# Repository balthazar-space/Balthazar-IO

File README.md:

# Balthazar

Open-hardware laptop computer modules description and concept.

These are electronic schematic modules as presented at https://balthazar.space/wiki/Balthazar with the main aim for team access. See the [main repository](https://github.com/balthazar-space/balthazar) for other designs.

# Balthazar IO

BalthazarIO module is a simple USB2.0 four-port hub for the internal devices: keyboard and touchpad, webcam and optional audiocard. Additional simplification and pcb size reduction was done recently.

IO-board (here) means connectivity with peripheral devices. These can be seen as on-board and out-board. On-board Balthazar devices include: combined usb1.1 keyboard + trackpad, usb2.0 webcam and optional audio-card. 

Since we are targeting the mini-computer family of systems (Raspberry PI. Banana PI, Orange PI, ...) - USB is the usual solution for this. 

A simple usb 2.0 hub is enough, so a very ubiquitous usb hub chip was chosen. Main mini-computer board usually provides a much better hub for 4 downstream usb devices. At this point this is still mainly USB 2.x - slowly moving to usb3.x.

Mass storage / system disk - microSD – and especially versions of SSD (sata or pcie) – should be plugged to usb3.x directly (via usb adapter).

KiCad 5.1.5 files are uploaded here as well as the drawings and pictures.

## License

All resources licensed under the CERN Open Hardware Licence CERN-OHL W V.2.0

Version 2.0 of the CERN-OHL introduces three variants of the licence – strongly (S) reciprocal, weakly (W) reciprocal and permissive (P) – which aim to address specific constraints caused by different collaboration models currently used in open-hardware projects. 

The first two variants mean that if any product is made using an open hardware design, the design of that product, including any improvements or modifications, should be made available under the same licence as that of the original product. Permissive licences do not impose this condition.

See the [LICENSE.md](./LICENSE.md) file for more information.

## Funding

This project is funded through the [NGI Zero Entrust Fund](https://nlnet.nl/entrust), a fund
established by [NLnet](https://nlnet.nl) with financial support from the European Commission's
[Next Generation Internet](https://ngi.eu) program. Learn more on the [NLnet project page](https://nlnet.nl/project/Balthazar-Casing/).

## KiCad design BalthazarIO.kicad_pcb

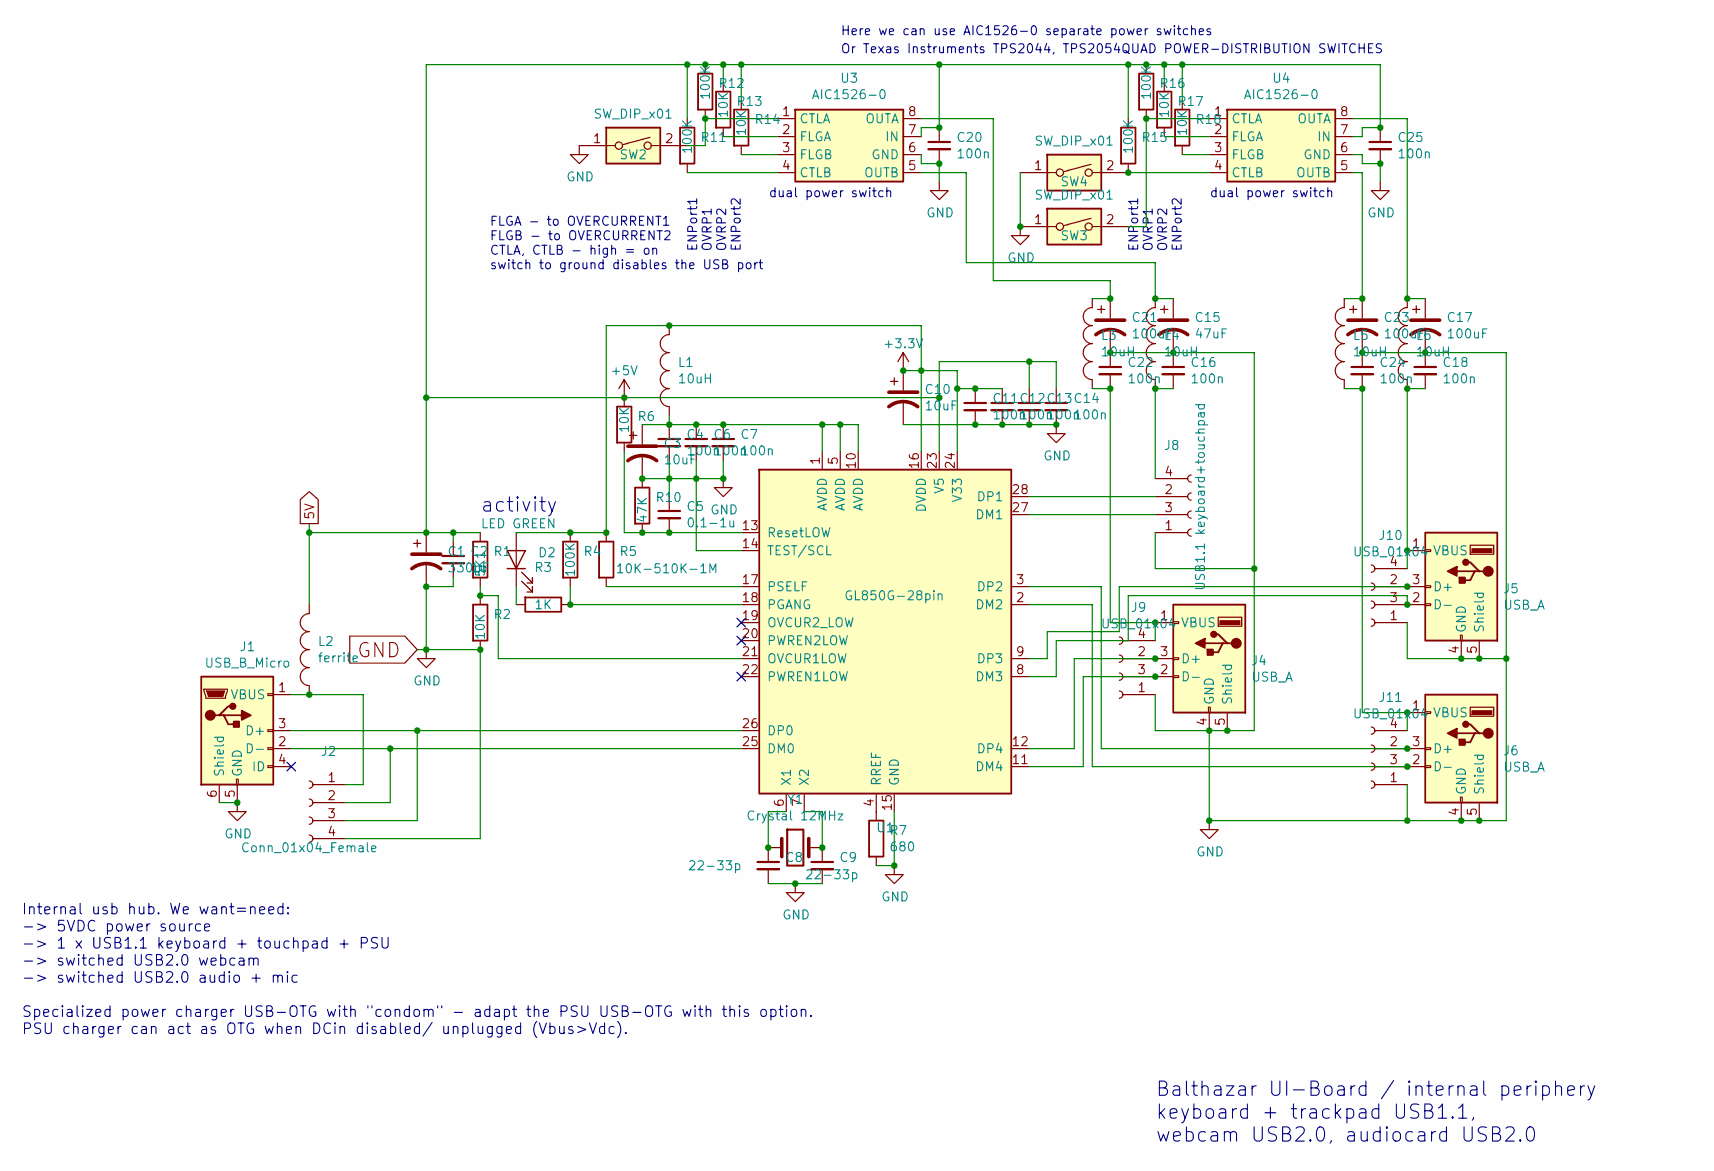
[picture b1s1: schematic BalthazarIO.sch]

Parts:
C1: 330uF; CP_Radial_D6.3mm_P2.50mm
C2: 1u; C_1206_3216Metric
C3, C10: 10uF; C_1206_3216Metric
C4, C6, C7, C11, C12, C13, C14, C16, C18, C20, C22, C24, C25: 100n; C_1206_3216Metric
C5: 0.1-1u; C_1206_3216Metric
C8, C9: 22-33p; C_1206_3216Metric
C15: 47uF; CP_Radial_D5.0mm_P2.50mm
C17, C21, C23: 100uF; CP_Radial_D5.0mm_P2.50mm
D2: LED GREEN; LED_1206_3216Metric
J1: USB_B_Micro; USB_Micro-AB_Molex_47590-0001
J2: Conn_01x04_Female; PinSocket_1x04_P2.54mm_Horizontal
J4, J5, J6: USB_A; USB_A_CNCTech_1001-011-01101_Horizontal
J8: USB1.1 keyboard+touchpad; PinSocket_1x04_P2.54mm_Horizontal
J9, J10, J11: USB_01x04; PinSocket_1x04_P2.54mm_Horizontal
L1, L3, L4, L5, L6: 10uH; L_1206_3216Metric
L2: ferrite; L_1206_3216Metric
R1: 5K1; R_1206_3216Metric
R2, R6, R13, R14, R17, R18: 10K; R_1206_3216Metric
R3: 1K; R_1206_3216Metric
R4, R11, R12, R15, R16: 100K; R_1206_3216Metric
R5: 10K-510K-1M; R_1206_3216Metric
R7: 680; R_1206_3216Metric
R10: 47K; R_1206_3216Metric
SW2, SW3, SW4: SW_DIP_x01; SW_DIP_SPSTx01_Slide_9.78x4.72mm_W7.62mm_P2.54mm
U1: GL850G-28pin; SSOP-28_5.3x10.2mm_P0.65mm
U3, U4: AIC1526-0; SOP-8_3.9x4.9mm_P1.27mm
Y1: Crystal 12MHz; Crystal_HC50_Vertical

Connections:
5V: C1.1, C2.1, C13.1, C14.1, C20.1, C25.1, L2.2, R1.1, R6.1, R11.1, R12.1, R13.1, R14.1, R15.1, R16.1, R17.1, R18.1, U1.23 (V5), U3.7 (IN), U4.7 (IN)
+3V3: C10.1, C11.1, C12.1, D2.2 (A), L1.2, R4.1, R5.1, U1.16 (DVDD), U1.24 (V33)
GND: C1.2, C2.2, C3.2, C4.2, C5.1, C6.2, C7.2, C8.2, C9.2, C10.2, C11.2, C12.2, C13.2, C14.2, C15.2, C16.1, C17.2, C18.1, C20.2, C21.2, C22.1, C23.2, C24.1, C25.2, J1.5 (GND), J1.6 (Shield), J2.4, J4.4 (GND), J4.5 (Shield), J5.4 (GND), J5.5 (Shield), J6.4 (GND), J6.5 (Shield), J8.1 (Vbus), J9.1 (Vbus), J10.1 (Vbus), J11.1 (Vbus), R2.2, R7.2, R10.1, SW2.1, SW3.1, SW4.1, U1.14 (TEST/SCL), U1.15 (GND), U3.6 (GND), U4.6 (GND)
unnamed: C3.1, C4.1, C6.1, C7.1, L1.1, U1.1 (AVDD), U1.5 (AVDD), U1.10 (AVDD)
unnamed: C5.2, R6.2, R10.2, U1.13 (ResetLOW)
unnamed: C8.1, U1.6 (X1), Y1.1
unnamed: C9.1, U1.7 (X2), Y1.2
unnamed: C15.1, L4.2, U3.5 (OUTB)
unnamed: C16.2, J8.4 (gnd), L4.1
unnamed: C17.1, L6.2, U4.8 (OUTA)
unnamed: C18.2, J5.1 (VBUS), J10.4 (gnd), L6.1
unnamed: C21.1, L3.2, U3.8 (OUTA)
unnamed: C22.2, J4.1 (VBUS), J9.4 (gnd), L3.1
unnamed: C23.1, L5.2, U4.5 (OUTB)
unnamed: C24.2, J6.1 (VBUS), J11.4 (gnd), L5.1
unnamed: D2.1 (K), R3.2
unnamed: J1.1 (VBUS), J2.1, L2.1
unnamed: J1.2 (D-), J2.2, U1.25 (DM0)
unnamed: J1.3 (D+), J2.3, U1.26 (DP0)
unnamed: J4.2 (D-), J9.3, U1.11 (DM4)
unnamed: J4.3 (D+), J9.2, U1.12 (DP4)
unnamed: J8.2, U1.28 (DP1)
unnamed: J8.3, U1.27 (DM1)
unnamed: J5.3 (D+), J10.2, U1.9 (DP3)
unnamed: J5.2 (D-), J10.3, U1.8 (DM3)
unnamed: J6.3 (D+), J11.2, U1.3 (DP2)
unnamed: J6.2 (D-), J11.3, U1.2 (DM2)
unnamed: R1.2, R2.1, U1.21 (OVCUR1LOW)
unnamed: R3.1, R4.2, U1.18 (PGANG)
unnamed: R5.2, U1.17 (PSELF)
unnamed: R7.1, U1.4 (RREF)
unnamed: R11.2, U3.4 (CTLB)
unnamed: R12.2, SW2.2, U3.1 (CTLA)
unnamed: R13.2, U3.2 (FLGA)
unnamed: R14.2, U3.3 (FLGB)
unnamed: R15.2, SW4.2, U4.4 (CTLB)
unnamed: R16.2, SW3.2, U4.1 (CTLA)
unnamed: R17.2, U4.2 (FLGA)
unnamed: R18.2, U4.3 (FLGB)

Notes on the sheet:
Balthazar UI-Board / internal periphery keyboard + trackpad USB1.1, webcam USB2.0, audiocard USB2.0
activity
Internal usb hub. We want=need: -> 5VDC power source -> 1 x USB1.1 keyboard + touchpad + PSU -> switched USB2.0 webcam -> switched USB2.0 audio + mic Specialized power charger USB-OTG with "condom" - adapt the PSU USB-OTG with this option. PSU charger can act as OTG when DCin disabled/ unplugged (V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
Here we can use AIC1526-0 separate power switches
ENPort1 OVRP1 OVRP2 ENPort2
dual power switch
Or Texas Instruments TPS2044, TPS2054QUAD POWER-DISTRIBUTION SWITCHES
FLGA - to OVERCURRENT1 FLGB - to OVERCURRENT2 CTLA, CTLB - high = on switch to ground disables the USB port

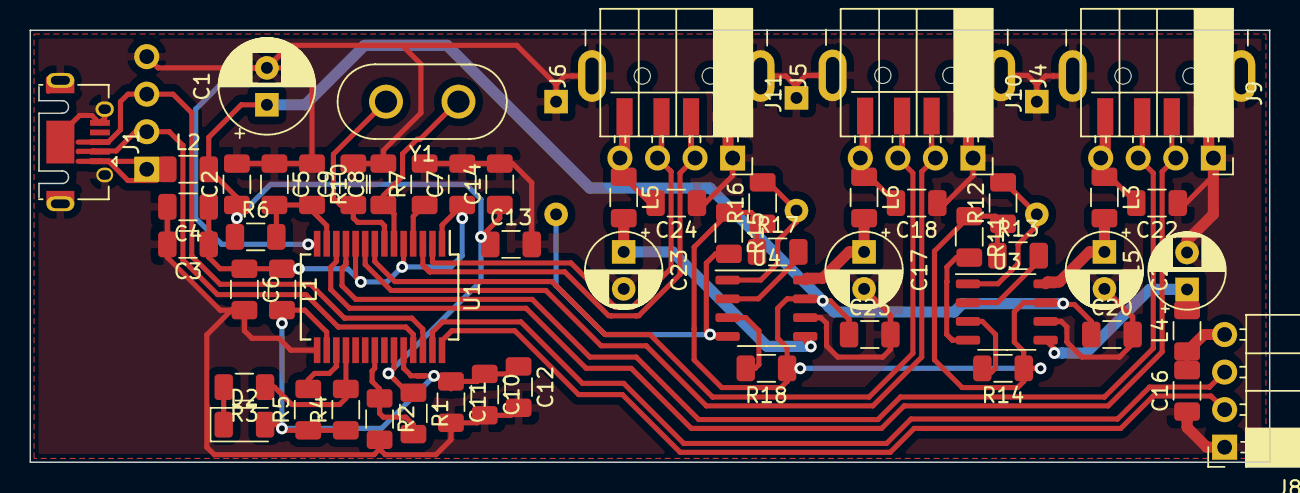
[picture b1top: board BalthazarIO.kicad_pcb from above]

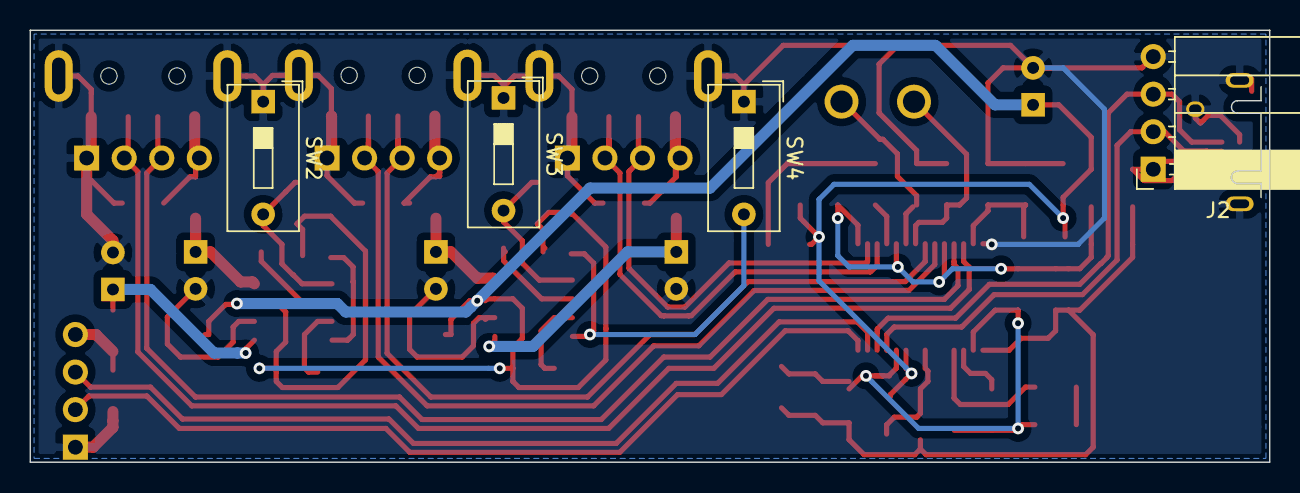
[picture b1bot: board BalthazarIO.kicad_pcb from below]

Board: 2 copper layers, 83.8 x 29.2 mm, 63 parts (4 on the bottom side), 39 nets.

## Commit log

2020-05-19 Create LICENSE
2020-06-19 NGI0-FSFE: Updating license file to include full license text
2021-07-28 admin
2024-06-25 Readme update (license, consistency)
2024-06-25 Add link to main repo
